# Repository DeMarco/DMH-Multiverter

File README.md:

# DMH-Multiverter
Mult and Attenuvater module in Kosmo format

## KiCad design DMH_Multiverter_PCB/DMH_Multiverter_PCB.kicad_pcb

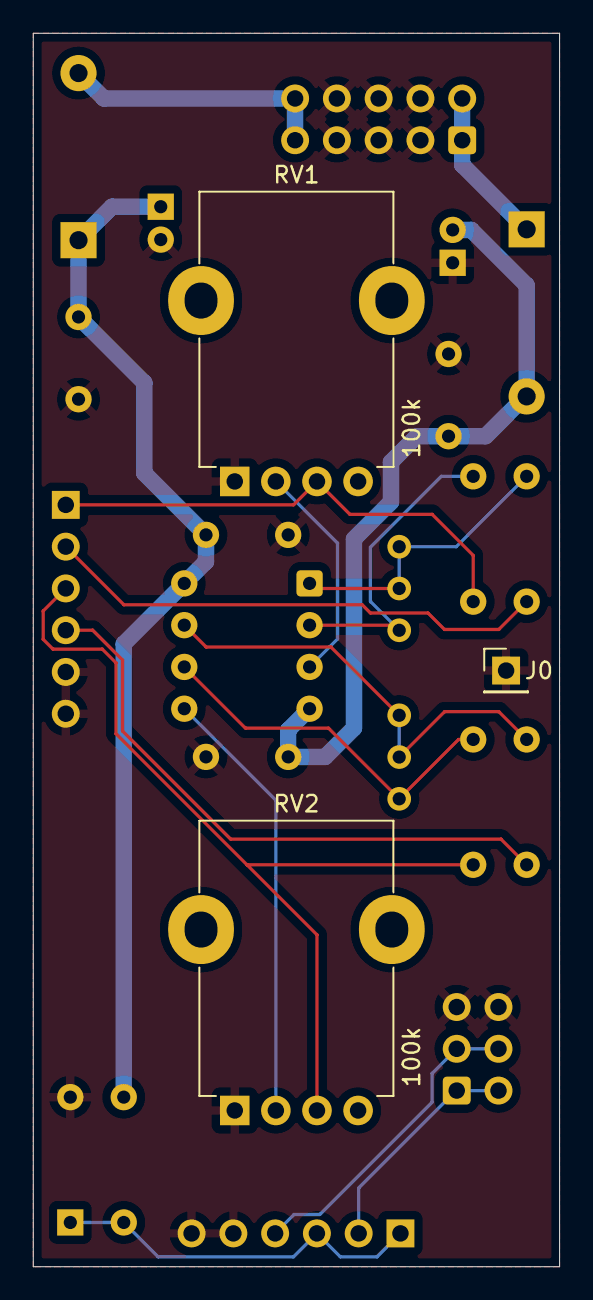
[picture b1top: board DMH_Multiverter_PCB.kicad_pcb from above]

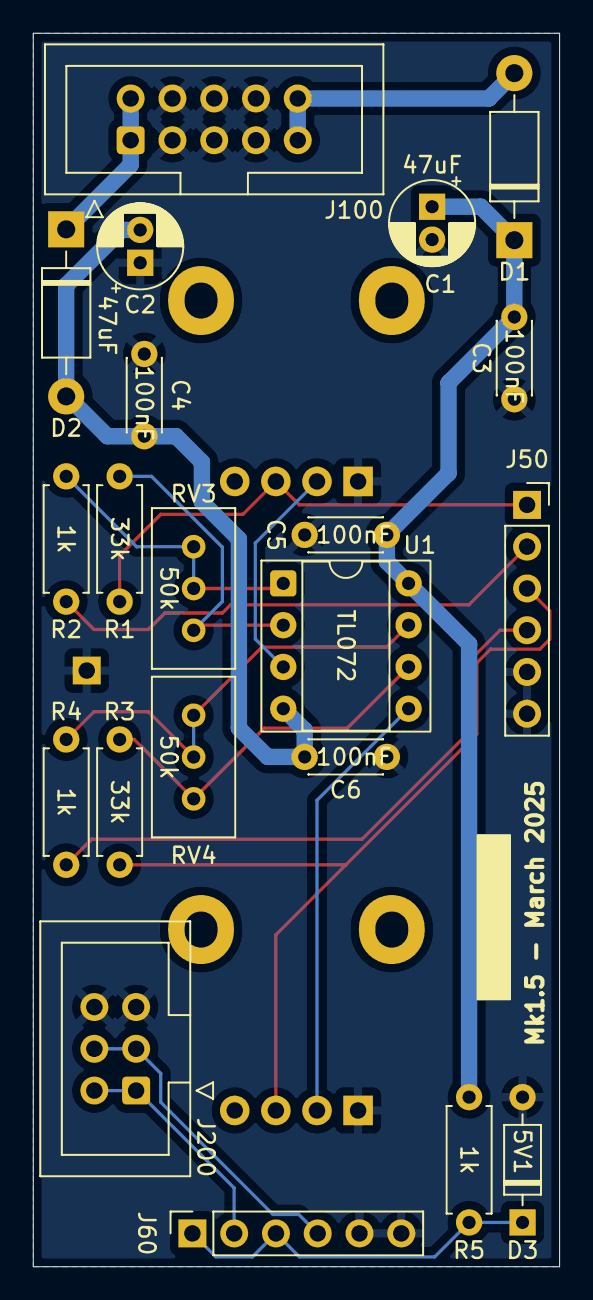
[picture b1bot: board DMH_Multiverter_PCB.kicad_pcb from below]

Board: 2 copper layers, 32.0 x 75.0 mm, 24 parts (21 on the bottom side), 18 nets.

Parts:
C1, C2: 47uF; CP_Radial_D5.0mm_P2.00mm
C3, C4, C5, C6: 100nF; C_Disc_D4.3mm_W1.9mm_P5.00mm
D1: SB140+; D_DO-41_SOD81_P10.16mm_Horizontal
D2: SB140-; D_DO-41_SOD81_P10.16mm_Horizontal
D3: ZPD5V1; D_DO-35_SOD27_P7.62mm_Horizontal
J0: Conn_01x01; PinHeader_1x01_P2.54mm_Vertical
J50, J60: Conn_01x06; PinSocket_1x06_P2.54mm_Vertical
J100: IDC_02x05; IDC-Header_2x05_P2.54mm_Vertical_Eurorack
J200: BackBone_Connector_6pin; IDC-Header_2x03_P2.54mm_Vertical_BackBone
R1, R3: 33k; R_Axial_DIN0207_L6.3mm_D2.5mm_P7.62mm_Horizontal
R2, R4, R5: 1k; R_Axial_DIN0207_L6.3mm_D2.5mm_P7.62mm_Horizontal
RV1, RV2: 100k; Potentiometer_TT_P110KH1
RV3, RV4: 50k; Potentiometer_Bourns_3296W_Vertical
U1: TL072; DIP-8_W7.62mm_Socket

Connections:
+12V: C1.1, C3.1, C5.1, D1.1 (K), R5.2, U1.8 (V+)
-12V: C2.2, C4.2, C6.2, D2.2 (A), U1.4 (V-)
/Core Circuit/Att A Input: J50.1, R1.1, RV1.3
/Core Circuit/Att A Output: J50.2, R2.2
/Core Circuit/Att B Input: J50.3, R3.1, RV2.3
/Core Circuit/Att B Output: J50.4, R4.2
GND: C1.2, C2.1, C3.2, C4.1, C5.2, C6.1, D3.2 (A), J0.1, J50.5, J50.6, J60.5, J60.6, J100.2a, J100.2b, J100.3a, J100.3b, J100.4a, J100.4b, J200.3, J200.6, RV1.1, RV2.1
unnamed: D1.2 (A), J100.5a, J100.5b
unnamed: D2.1 (K), J100.1a, J100.1b
unnamed: D3.1 (K), J60.1, J60.3, R5.1
unnamed: J60.2, J200.1, J200.4
unnamed: J60.4, J200.2, J200.5
unnamed: R2.1, RV3.2, RV3.3, U1.1
unnamed: R4.1, RV4.2, RV4.3, U1.7
unnamed: RV1.2, U1.3 (+)
unnamed: R1.2, RV3.1, U1.2 (-)
unnamed: RV2.2, U1.5 (+)
unnamed: R3.2, RV4.1, U1.6 (-)

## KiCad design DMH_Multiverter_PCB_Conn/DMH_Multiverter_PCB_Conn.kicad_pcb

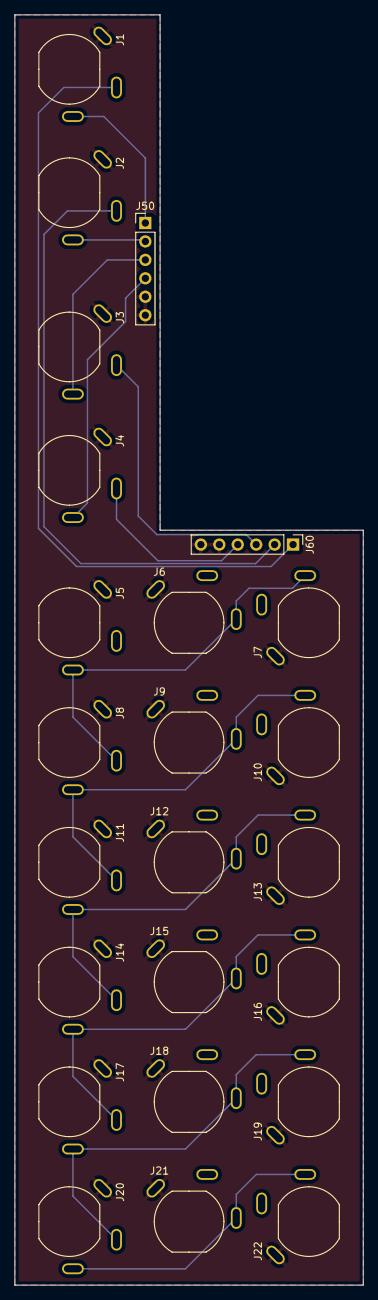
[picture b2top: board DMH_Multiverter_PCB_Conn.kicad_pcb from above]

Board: 2 copper layers, 48.0 x 175.0 mm, 24 parts (0 on the bottom side), 15 nets.

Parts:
J1, J2, J3, J4, J5, J6, J7, J8, J9, J10, J11, J12, J13, J14, J15, J16, J17, J18, J19, J20, J21, J22: TS_Jack_6.35mm_Sw; CUI_MJ-63052A
J50, J60: Conn_01x06; PinHeader_1x06_P2.54mm_Vertical

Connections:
/Inputs and Outputs/Att A Input Jack: J1.T, J50.1
/Inputs and Outputs/Att A Output Jack: J2.T, J50.2
/Inputs and Outputs/Att B Input Jack: J3.T, J50.3
/Inputs and Outputs/Att B Output Jack: J4.T, J50.4
GND: J1.S, J2.S, J3.S, J4.S, J5.S, J6.S, J7.S, J8.S, J9.S, J10.S, J11.S, J12.S, J13.S, J14.S, J15.S, J16.S, J17.S, J18.S, J19.S, J20.S, J21.S, J22.S, J50.5, J50.6, J60.5, J60.6
unnamed: J5.T, J6.T, J7.T, J8.TN
unnamed: J8.T, J9.T, J10.T, J11.TN
unnamed: J11.T, J12.T, J13.T, J14.TN
unnamed: J14.T, J15.T, J16.T, J17.TN
unnamed: J17.T, J18.T, J19.T, J20.TN
unnamed: J20.T, J21.T, J22.T
unnamed: J1.TN, J60.1
unnamed: J2.TN, J60.2
unnamed: J3.TN, J60.3
unnamed: J4.TN, J60.4

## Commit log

2024-11-26 Created Kicad projects
2024-11-26 Panel ready
2024-11-26 Finished schematic
2024-11-26 Placed components in PCB
2024-11-26 Finished PCB Conn schematic
2024-11-26 Finished conn PCB
2024-11-27 Adapted design to center detent pot P110KH-1F15
2024-11-28 Fixed P110H1 bracket hole size
2024-12-03 Created Gerbers
2024-12-08 Generated BoM
2024-12-22 Re-routing ongoing
2024-12-22 Finished routing Mk2 version
2024-12-22 Sync libs
2024-12-27 Testing out CV offset output feature
2024-12-28 Enabled txt files and added falstad simulation
2024-12-28 Testing attenuverter calibration
2024-12-28 Finished Mk2 design
    - Changed R7 value to 10k
    - Replaced the other resistor with a 5V1 Zener
    - Cleaned up schematic
2024-12-31 Switched adjustment trimpots position with Rin
    ... and renumbered the resistors.
2025-02-22 converted to kc9
2025-02-23 Converted rest to KiCad 9
2025-03-02 Generated PCB Mk1.5 Gerbers
2025-03-09 Changed normalled DC offset resistor to 1k
2025-03-15 Regenerated Gerbers
2025-12-06 KiCad 9
